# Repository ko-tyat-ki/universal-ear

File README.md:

# Nowhere Ear

```
Isn't he a bit like you and me?
Nowhere man, The world is at your command
```
## Introduction

You all know that we, the Ko-Tyat-Ki Kollektive, are working on this crazy
installation **EAR OF THE UNIVERSE** that will be (wooop wooop)
premiered at Nowhere 2019.

How do you create visuals for an installation you can't practically build at home?
That is correct, as a Full Stack dev, you create a web-simulation of the
real installation you can practice your code on 😆.

And then you ask all your friends to contribute!

## About the installation

The principle is:
a lot of ropes, when people touch them or pull them, the LEDs and
sound-scape changes.

How the light changes can be decided by you!

In this simulation, you can simulate pulling the ropes by
pressing keys on the keyboard, and see the results on the web page.

## Your contribution!

We worked very hard to make a potential contribution as easy as possible.
All the visualisation, simulation is there, but we need your ideas on how
to transform sensor data into lit LEDs.

This is basically to create a bit of a transformation code in between.

We did come up with several examples that represent what potantially can be done.
We hope they will be helpful, but please feel free to go wild.

When we recieve all the beautiful ideas, we will select the best, and figure out the
way to present them (e.g. one stick per idea? or one hour gig for each idea?)

And your idea and your name will be on Playa making all of nobodies super happy.

_(more details and explanations on where and how exactly to fill your idea in below)_

## Pre-requirements

Very basic knowledge of any coding and github should be enough.

Technical prerequisites: [github account](https://help.github.com/en/articles/connecting-to-github-with-ssh), computer with installed and [set up git](https://git-scm.com/book/en/v2/Getting-Started-First-Time-Git-Setup), [node and npm](https://www.npmjs.com/get-npm) (we use node 10).

## As a start
```
git clone git@github.com:ko-tyat-ki/nowhere-ear.git
cd nowhere-ear
npm install
npm start
```

This will start node server that will restart when you change the code.
Code can be written using es2015 syntax on server and on client.

When starting the server you might notice some warnings in the console, e.g.
```
Warning: the port /dev/tty/.usbmodem14201 failed to open, did you connect the device? If not - no worries, client side can work without it
```
Do not worry, this is for us to monitor the real devices we sometimes connect. The simulation can work without them.

#### To see the results
Navigate to http://localhost:3000 in your browser and enjoy the visualisation:

You can see three *structure types*: "Duet", "Circle" and "Realistic".
"Realistic" is the main one that is very similar to our latest plans for the real thing. Scaffolding position are close to what we are planning in reality. LEDs position are indicative, and might change - so this is mainly for you to have an idea / rough understanding how it is going to look. It will look much cooler with sensors highlighting fluorescent ropes and stuff (hopefully).

To "trigger" the sensor you can use keys "a" and "s" for "Duet", and
"1","2","3","4","5","6","7","8","9","0" for "Circle" and "Realistic".

We did simulate two types of interaction - very fast one, similar to abruptly pulling
the rope (keep the key on for a short period of time), and smooth one (keep key for a bit longer).

You can already choose several visual *modes* - functions that transform sensor data into lit leds. These are very basic examples of what potentially can be done (more about this below).

## How to contribute

### How can you add a new visualisation
1. Create a new branch with a name for example `[your-name]-[mode-name]` e.g. `katya-supermegacoolmode`

```
git checkout -b [your-name]-[mode-name]
```

2. Go to the folder `./web/lib/modes/`. This is where all visual modes live. Create a js file where your code will live (the easiest might be by copying one of the existing ones?).

3. Import it into `./web/lib/visualisations.js` by adding

```js
import [yourMode] from './modes/[yourMode]'
```

and the name of it to export.

4. Add a new mode under the same name `./static/index.html` under `<h5>mode:</h5>`

```html
<option value="yourMode">How you want to show your mode</option>
```

5. When you are happy with what you've done, create a Pull Request, and tag some of us.

### A bit more about modes

Modes function accepts `(sticks, sensors)`.

From sticks you can use properties that are set on config, such as
- `name`
- `numberOfLEDs`
- inital coordinates (y is vertical)
```js
init : {
    x: ...,
    y: ...,
    z: ...
}
```
Senors have
 - `tension` - the tension that depends on key press. There are two distinct tension modes,
 -- if the user releases the key after less than 0.5s pressing, the sensor gets quickly to the highest value and back
 -- if the user continues pressing the key after 0.5s, the sensor value slowly increases, and slowly decreases after the button is released
 - `oldTension` - an array of tension history (four values slowly following the current tension value: [0] the furthest away from tension value, [3] the closest value)
 - `stick` - which column (stick) it is attached to
 - `position` - where on the stick it is attached to; as a number of the LED

The function should return array of arrays, where every entry has
- `key` - name of the stick you want to light up
- array of `leds`.

Every led has its `number` (integer, from `0` to `numberOfLEDs-1`) and color
```js
color : {
    r: ...,
    g: ...,
    b: ...
}
```

Everything else is up to your imagination.

## A bit more about existing examples

### Basic

Simply reacts to sensor tension proportionate to tension. Very basic.

### Fast reaction

Reacts only to fast pull and does not to slow one.

### Flicker

Flickers the stick when you activate the sensor attahced to it.

### Random echo

The active stick is the brightest, all the rest are less bright proportinate to the distance.

### Tension with echo

When tension reached the end of the stick, its echo goes to all other sticks.

## Support and questions

Any questions, suggestions, love notes - write them either to Katya or Ivan immediately via
any known source of commmunication, or submit a github issue.

## API

### Switch mode

Path: `/mode`
Method: `POST`
Headers: `Content-Type: application/json`
Body Example:
```
{
  "method": "flicker"
}
```

Available modes:
```
basic
basic_with_rainbow
changing_colors
fastReaction
flicker
rain
rainEffect
random_flashes
randomEcho
tensionWithEcho
workshop
```

## Helpful commands
To list connected USB devices
```
ls /dev/tty*
```
To get the sound working run in the parallel terminal
```
python3 ./sound/run_sound.py
```
Make sure you have `pygame` installed. If you see an error message
`ImportError: No module named pygame` 
```
python -m ensurepip --user
/Library/Developer/CommandLineTools/usr/bin/python3 -m pip install --upgrade pip
python -m pip install pygame
```
Connect to PI SD card from comp:
```
sudo kextunload -b io.macfuse.filesystems.macfuse
sudo fuse-ext2 /dev/disk4s2 /Volumes/raspberry -o rw+
```
## How to change wifi data
```
cd /Volumes/raspberry/home/pi/nowhere-ear/deploy/pi-settings
vim wpa_supplicant.conf
```
Then
```
cd /
sudo umount /Volumes/raspberry
```
Sometimes you have to relogin to pi, passowrd is `raspberry`

sudo amixer cset numid=1 90%

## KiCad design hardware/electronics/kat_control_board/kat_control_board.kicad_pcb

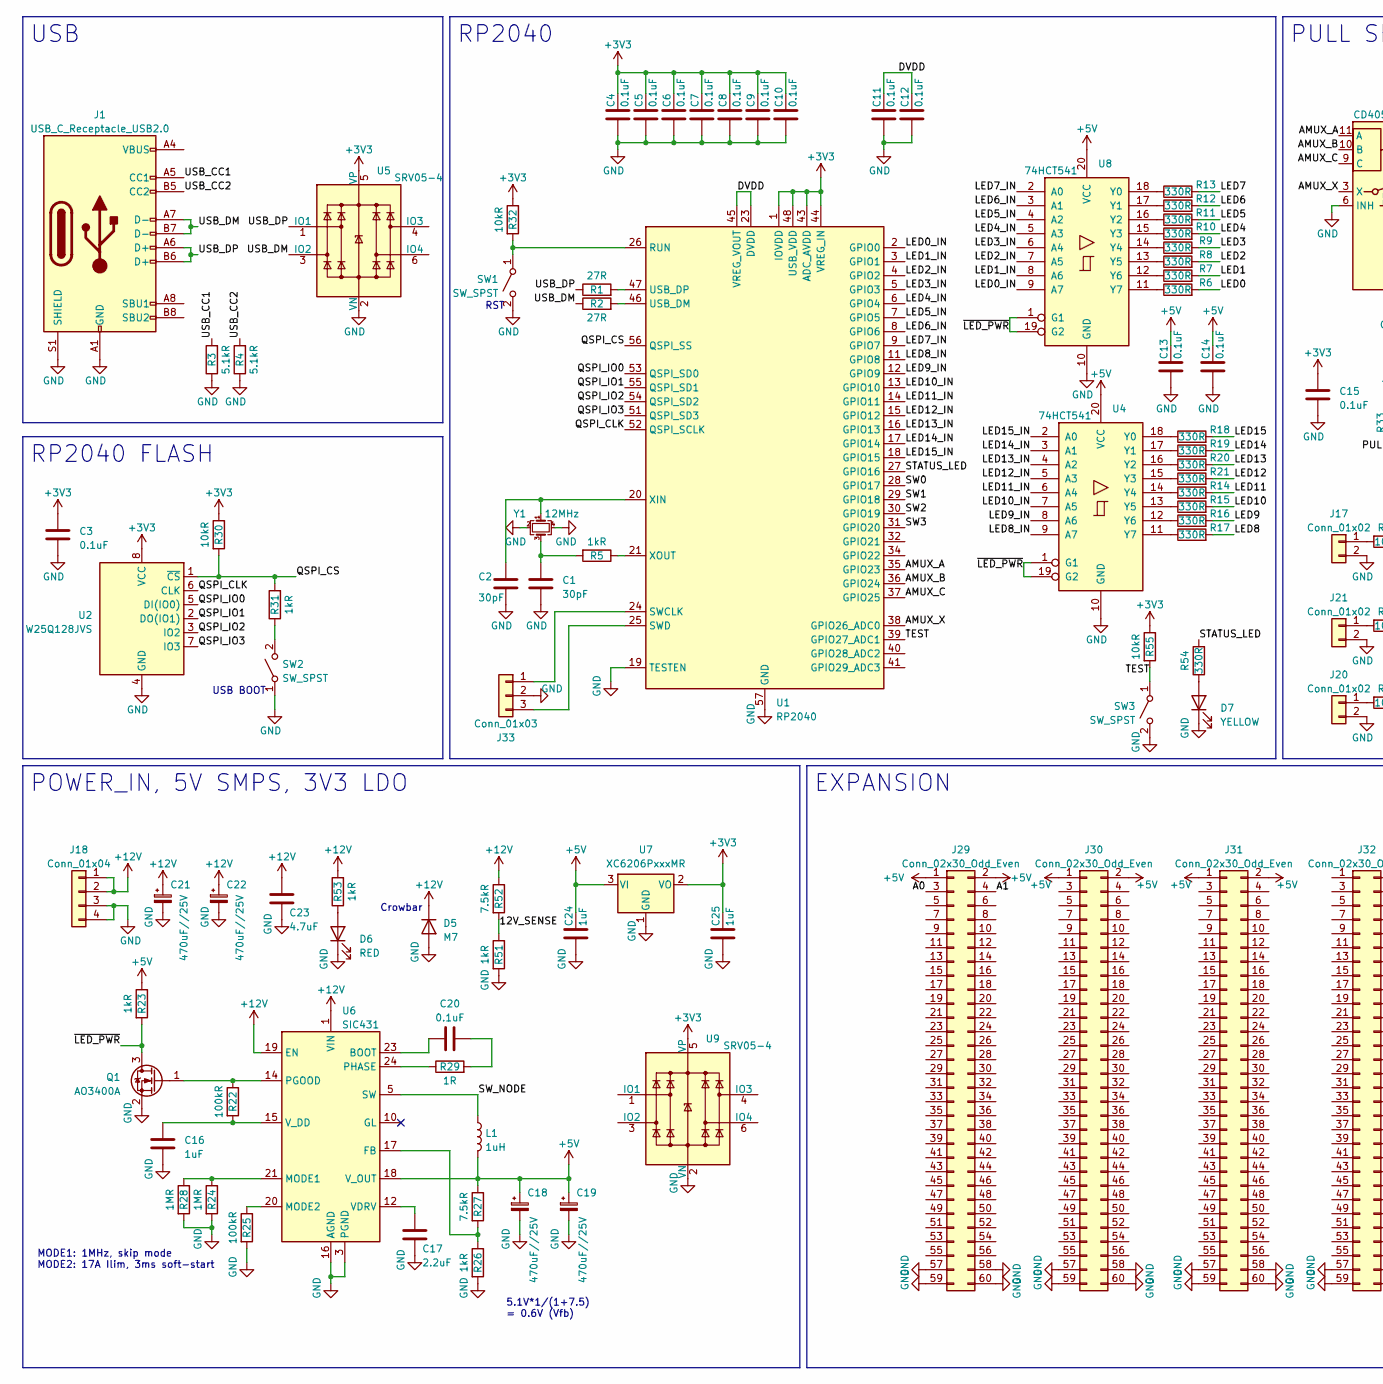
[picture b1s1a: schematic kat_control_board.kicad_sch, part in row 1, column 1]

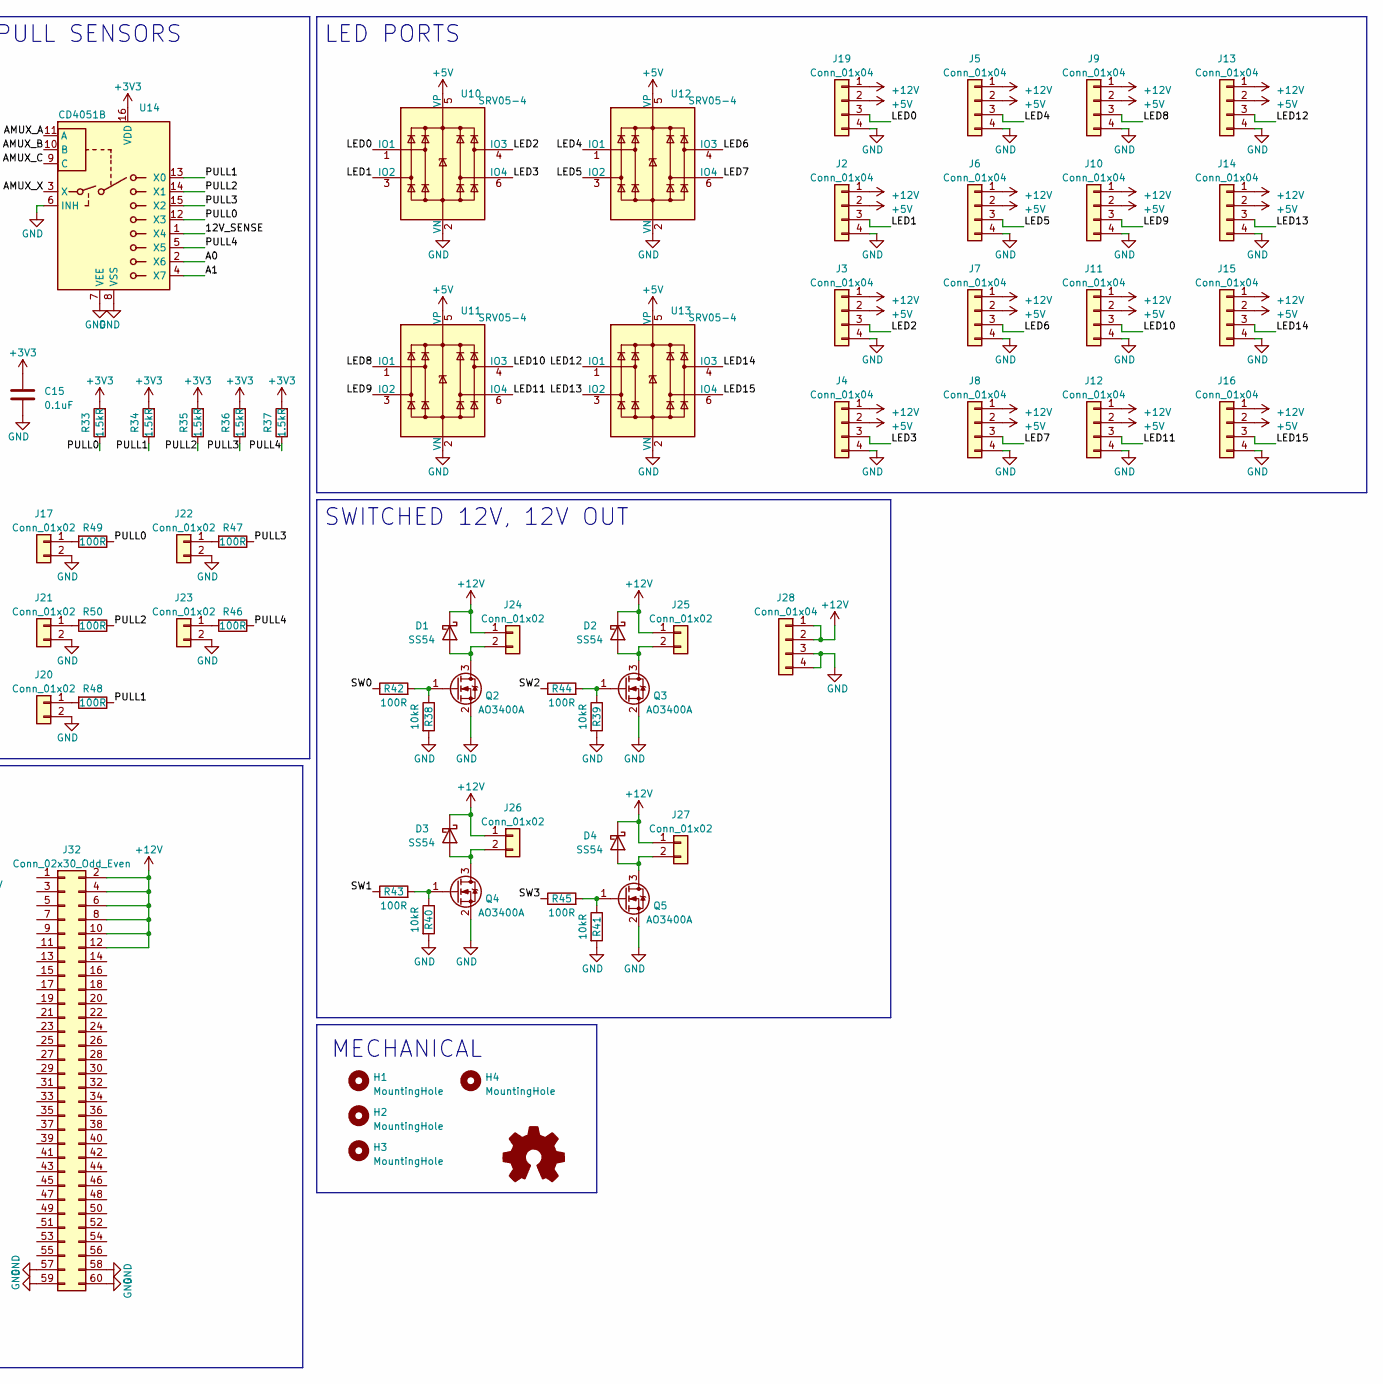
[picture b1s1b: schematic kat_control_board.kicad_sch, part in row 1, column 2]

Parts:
C1, C2: 30pF; C_0402_1005Metric; JLC C1570
C3, C4, C5, C6, C7, C8, C9, C10, C11, C12, C13, C14, C15: 0.1uF; C_0402_1005Metric; JLC C1525
C16, C24, C25: 1uF; C_0402_1005Metric; JLC C52923
C17: 2.2uF; C_0603_1608Metric; JLC C23630
C18, C19, C21, C22: 470uF//25V; CP_Radial_D6.3mm_P2.50mm; JLC C2938714
C20: 0.1uF; C_0402_1005Metric; JLC C307331
C23: 4.7uF; C_0603_1608Metric; JLC C19666
D1, D2, D3, D4: SS54; D_SMA; LCSC C22452
D5: M7; D_SMA; LCSC C95872
D6: RED; LED_0603_1608Metric; LCSC C2286
D7: YELLOW; LED_0603_1608Metric; LCSC C72038
H1, H2, H3, H4: MountingHole; MountingHole_3.5mm_Pad_Via
J1: USB_C_Receptacle_USB2.0; USB_C_Receptacle_HRO_TYPE-C-31-M-12; JLC C165948
J2, J3, J4, J5, J6, J7, J8, J9, J10, J11, J12, J13, J14, J15, J16, J18, J19, J28: Conn_01x04; DB2ERC-3.5-4P; JLC C395831
J17, J20, J21, J22, J23, J24, J25, J26, J27: Conn_01x02; DB2ERC-3.5-2P; LCSC C395830
J29, J30, J31, J32: Conn_02x30_Odd_Even; PinHeader_2x30_P2.54mm_Vertical
J33: Conn_01x03; PinHeader_1x03_P2.54mm_Vertical
L1: 1uH; CKST1004; JLC C3002679
LOGO1: Logo_Open_Hardware_Small; kinki_yokai_logo
Q1: AO3400A; SOT-23; JLC C20917
Q2, Q3, Q4, Q5: AO3400A; SOT-23; LCSC C20917
R1, R2: 27R; R_0603_1608Metric; JLC C25190
R3, R4: 5.1kR; R_0402_1005Metric; JLC C105872
R5, R23, R26, R31, R51, R53: 1kR; R_0402_1005Metric; JLC C11702
R6, R7, R8, R9, R10, R11, R12, R13, R14, R15, R16, R17, R18, R19, R20, R21, R54: 330R; R_0402_1005Metric; JLC C25104
R22: 100kR; R_0402_1005Metric; JLC C25086
R24, R28: 1MR; R_0402_1005Metric; JLC C26083
R25: 100kR; R_0402_1005Metric; JLC C25741
R27, R52: 7.5kR; R_0402_1005Metric; JLC C25918
R29: 1R; R_0402_1005Metric; JLC C25086
R30, R32, R38, R39, R40, R41, R55: 10kR; R_0402_1005Metric; JLC C25086
R33, R34, R35, R36, R37: 1.5kR; R_0402_1005Metric; JLC C25867
R42, R43, R44, R45, R46, R47, R48, R49, R50: 100R; R_0402_1005Metric; JLC C25076
SW1, SW2, SW3: SW_SPST; TS-1187A-B-A-B; JLC C318884
U1: RP2040; QFN-56-1EP_7x7mm_P0.4mm_EP3.2x3.2mm; JLC C2040
U2: W25Q128JVS; SOIC-8_5.23x5.23mm_P1.27mm; JLC C97521
U4, U8: 74HCT541; TSSOP-20_4.4x6.5mm_P0.65mm; LCSC C436096
U5, U9, U10, U11, U12, U13: SRV05-4; SOT-23-6; LCSC C85364
U6: SIC431; Vishay_PowerPAK_MLP44-24L_ThermalVias; LCSC C2071422
U7: XC6206PxxxMR; SOT-23-3; LCSC C5446
U14: CD4051B; SOIC-16_3.9x9.9mm_P1.27mm; LCSC C21379
Y1: 12MHz; Crystal_SMD_3225-4Pin_3.2x2.5mm; JLC C9002

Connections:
+3V3: C3.1, C4.1, C5.1, C6.1, C7.1, C8.1, C9.1, C10.1, C15.1, C25.1, R30.1, R32.1, R33.2, R34.2, R35.2, R36.2, R37.2, R55.1, U1.1 (IOVDD), U1.10 (IOVDD), U1.22 (IOVDD), U1.33 (IOVDD), U1.42 (IOVDD), U1.43 (ADC_AVDD), U1.44 (VREG_IN), U1.48 (USB_VDD), U1.49 (IOVDD), U2.8 (VCC), U5.5 (VP), U7.2 (VO), U9.5 (VP), U14.16 (VDD)
+5V: C13.1, C14.1, C18.1, C19.1, C24.1, J2.2, J3.2, J4.2, J5.2, J6.2, J7.2, J8.2, J9.2, J10.2, J11.2, J12.2, J13.2, J14.2, J15.2, J16.2, J19.2, J29.1, J29.2, J30.1, J30.2, J31.1, J31.2, L1.2, R23.1, R27.1, U4.20 (VCC), U6.18 (V_OUT), U7.3 (VI), U8.20 (VCC), U10.5 (VP), U11.5 (VP), U12.5 (VP), U13.5 (VP)
+12V: C21.1, C22.1, C23.1, D1.1 (K), D2.1 (K), D3.1 (K), D4.1 (K), D5.1 (K), J2.1, J3.1, J4.1, J5.1, J6.1, J7.1, J8.1, J9.1, J10.1, J11.1, J12.1, J13.1, J14.1, J15.1, J16.1, J18.1, J18.2, J19.1, J24.1, J25.1, J26.1, J27.1, J28.1, J28.2, J32.2, J32.4, J32.6, J32.8, J32.10, J32.12, R52.1, R53.2, U6.1 (VIN), U6.2 (VIN), U6.19 (EN), U6.22 (VIN), U6.26 (VIN)
/12V_SENSE: R51.1, R52.2, U14.1 (X4)
/A0: J29.3, U14.2 (X6)
/A1: J29.4, U14.4 (X7)
/AMUX_A: U1.35 (GPIO23), U14.11 (A)
/AMUX_B: U1.36 (GPIO24), U14.10 (B)
/AMUX_C: U1.37 (GPIO25), U14.9 (C)
/AMUX_X: U1.38 (GPIO26_ADC0), U14.3 (X)
/DVDD: C11.1, C12.1, U1.23 (DVDD), U1.45 (VREG_VOUT), U1.50 (DVDD)
/LED0: J19.3, R6.2, U10.1 (IO1)
/LED0_IN: U1.2 (GPIO0), U8.9 (A7)
/LED1: J2.3, R7.2, U10.3 (IO2)
/LED1_IN: U1.3 (GPIO1), U8.8 (A6)
/LED2: J3.3, R8.2, U10.4 (IO3)
/LED2_IN: U1.4 (GPIO2), U8.7 (A5)
/LED3: J4.3, R9.2, U10.6 (IO4)
/LED3_IN: U1.5 (GPIO3), U8.6 (A4)
/LED4: J5.3, R10.2, U12.1 (IO1)
/LED4_IN: U1.6 (GPIO4), U8.5 (A3)
/LED5: J6.3, R11.2, U12.3 (IO2)
/LED5_IN: U1.7 (GPIO5), U8.4 (A2)
/LED6: J7.3, R12.2, U12.4 (IO3)
/LED6_IN: U1.8 (GPIO6), U8.3 (A1)
/LED7: J8.3, R13.2, U12.6 (IO4)
/LED7_IN: U1.9 (GPIO7), U8.2 (A0)
/LED8: J9.3, R17.2, U11.1 (IO1)
/LED8_IN: U1.11 (GPIO8), U4.9 (A7)
/LED9: J10.3, R16.2, U11.3 (IO2)
/LED9_IN: U1.12 (GPIO9), U4.8 (A6)
/LED10: J11.3, R15.2, U11.4 (IO3)
/LED10_IN: U1.13 (GPIO10), U4.7 (A5)
/LED11: J12.3, R14.2, U11.6 (IO4)
/LED11_IN: U1.14 (GPIO11), U4.6 (A4)
/LED12: J13.3, R21.2, U13.1 (IO1)
/LED12_IN: U1.15 (GPIO12), U4.5 (A3)
/LED13: J14.3, R20.2, U13.3 (IO2)
/LED13_IN: U1.16 (GPIO13), U4.4 (A2)
/LED14: J15.3, R19.2, U13.4 (IO3)
/LED14_IN: U1.17 (GPIO14), U4.3 (A1)
/LED15: J16.3, R18.2, U13.6 (IO4)
/LED15_IN: U1.18 (GPIO15), U4.2 (A0)
/PULL0: R33.1, R49.1, U14.12 (X3)
/PULL1: R34.1, R48.1, U14.13 (X0)
/PULL2: R35.1, R50.1, U14.14 (X1)
/PULL3: R36.1, R47.1, U14.15 (X2)
/PULL4: R37.1, R46.1, U14.5 (X5)
/QSPI_CLK: U1.52 (QSPI_SCLK), U2.6 (CLK)
/QSPI_CS: R30.2, R31.2, U1.56 (QSPI_SS), U2.1 (~CS)
/QSPI_IO0: U1.53 (QSPI_SD0), U2.5 (DI(IO0))
/QSPI_IO1: U1.55 (QSPI_SD1), U2.2 (DO(IO1))
/QSPI_IO2: U1.54 (QSPI_SD2), U2.3 (IO2)
/QSPI_IO3: U1.51 (QSPI_SD3), U2.7 (IO3)
/STATUS_LED: R54.2, U1.27 (GPIO16)
/SW0: R42.1, U1.28 (GPIO17)
/SW1: R43.1, U1.29 (GPIO18)
/SW2: R44.1, U1.30 (GPIO19)
/SW3: R45.1, U1.31 (GPIO20)
/SW_NODE: L1.1, U6.5 (SW), U6.6 (SW), U6.7 (SW), U6.8 (SW), U6.9 (SW)
/TEST: R55.2, SW3.1 (A), U1.39 (GPIO27_ADC1)
/USB_CC1: J1.A5 (CC1), R3.2
/USB_CC2: J1.B5 (CC2), R4.2
/USB_DM: J1.A7 (D-), J1.B7 (D-), R2.1, U5.3 (IO2)
/USB_DP: J1.A6 (D+), J1.B6 (D+), R1.1, U5.1 (IO1)
/~LED_PWR: Q1.3 (D), R23.2, U4.1 (G1), U4.19 (G2), U8.1 (G1), U8.19 (G2)
GND: C1.2, C2.2, C3.2, C4.2, C5.2, C6.2, C7.2, C8.2, C9.2, C10.2, C11.2, C12.2, C13.2, C14.2, C15.2, C16.2, C17.2, C18.2, C19.2, C21.2, C22.2, C23.2, C24.2, C25.2, D5.2 (A), D6.1 (K), D7.1 (K), J1.A1 (GND), J1.A12 (GND), J1.B1 (GND), J1.B12 (GND), J1.S1 (SHIELD), J2.4, J3.4, J4.4, J5.4, J6.4, J7.4, J8.4, J9.4, J10.4, J11.4, J12.4, J13.4, J14.4, J15.4, J16.4, J17.2, J18.3, J18.4, J19.4, J20.2, J21.2, J22.2, J23.2, J28.3, J28.4, J29.57, J29.58, J29.59, J29.60, J30.57, J30.58, J30.59, J30.60, J31.57, J31.58, J31.59, J31.60, J32.57, J32.58, J32.59, J32.60, J33.2, Q1.2 (S), Q2.2 (S), Q3.2 (S), Q4.2 (S), Q5.2 (S), R3.1, R4.1, R24.2, R25.2, R26.2, R28.2, R38.2, R39.2, R40.2, R41.2, R51.2, SW1.2 (B), SW2.1 (A), SW3.2 (B), U1.19 (TESTEN), U1.57 (GND), U2.4 (GND), U4.10 (GND), U5.2 (VN), U6.3 (PGND), U6.4 (PGND), U6.13 (PGND), U6.16 (AGND), U6.25 (AGND), U6.27 (PGND), U7.1 (GND), U8.10 (GND), U9.2 (VN), U10.2 (VN), U11.2 (VN), U12.2 (VN), U13.2 (VN), U14.6 (INH), U14.7 (VEE), U14.8 (VSS), Y1.2, Y1.4
unnamed: C1.1, R5.2, Y1.3
unnamed: C20.2, R29.2
unnamed: D1.2 (A), J24.2, Q2.3 (D)
unnamed: D2.2 (A), J25.2, Q3.3 (D)
unnamed: D3.2 (A), J26.2, Q4.3 (D)
unnamed: D4.2 (A), J27.2, Q5.3 (D)
unnamed: D6.2 (A), R53.1
unnamed: D7.2 (A), R54.1
unnamed: J1.A4 (VBUS), J1.A9 (VBUS), J1.B4 (VBUS), J1.B9 (VBUS)
unnamed: J17.1, R49.2
unnamed: J20.1, R48.2
unnamed: J21.1, R50.2
unnamed: J22.1, R47.2
unnamed: J23.1, R46.2
unnamed: J33.1, U1.24 (SWCLK)
unnamed: J33.3, U1.25 (SWD)
unnamed: Q1.1 (G), R22.1, U6.14 (PGOOD)
unnamed: Q2.1 (G), R38.1, R42.2
unnamed: Q3.1 (G), R39.1, R44.2
unnamed: Q4.1 (G), R40.1, R43.2
unnamed: Q5.1 (G), R41.1, R45.2
unnamed: R32.2, SW1.1 (A), U1.26 (RUN)
unnamed: R31.1, SW2.2 (B)
unnamed: R2.2, U1.46 (USB_DM)
unnamed: R1.2, U1.47 (USB_DP)
unnamed: C2.1, U1.20 (XIN), Y1.1
unnamed: R5.1, U1.21 (XOUT)
unnamed: R18.1, U4.18 (Y0)
unnamed: R19.1, U4.17 (Y1)
unnamed: R20.1, U4.16 (Y2)
unnamed: R21.1, U4.15 (Y3)
unnamed: R14.1, U4.14 (Y4)
unnamed: R15.1, U4.13 (Y5)
unnamed: R16.1, U4.12 (Y6)
unnamed: R17.1, U4.11 (Y7)
unnamed: C20.1, U6.23 (BOOT)
unnamed: R26.1, R27.2, U6.17 (FB)
unnamed: R24.1, R28.1, U6.21 (MODE1)
unnamed: R25.1, U6.20 (MODE2)
unnamed: R29.1, U6.24 (PHASE)
unnamed: C17.1, U6.12 (VDRV)
unnamed: C16.1, R22.2, U6.15 (V_DD)
unnamed: R13.1, U8.18 (Y0)
unnamed: R12.1, U8.17 (Y1)
unnamed: R11.1, U8.16 (Y2)
unnamed: R10.1, U8.15 (Y3)
unnamed: R9.1, U8.14 (Y4)
unnamed: R8.1, U8.13 (Y5)
unnamed: R7.1, U8.12 (Y6)
unnamed: R6.1, U8.11 (Y7)

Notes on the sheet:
SWITCHED 12V, 12V OUT
LED PORTS
RP2040 FLASH
Crowbar
MODE1: 1MHz, skip mode MODE2: 17A Ilim, 3ms soft-start
EXPANSION
5.1V*1/(1+7.5) = 0.6V (Vfb)
USB BOOT
USB
PULL SENSORS
MECHANICAL
RST
POWER_IN, 5V SMPS, 3V3 LDO
RP2040

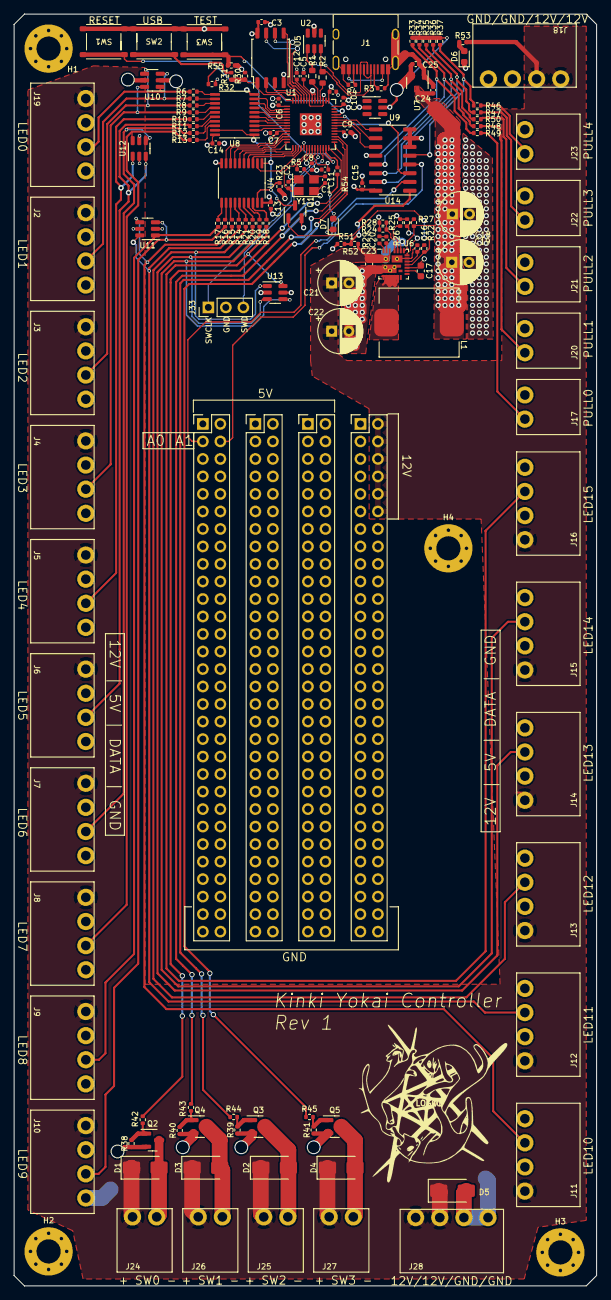
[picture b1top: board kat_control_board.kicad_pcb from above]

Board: 4 copper layers, 84.5 x 184.5 mm, 148 parts (0 on the bottom side), 117 nets.

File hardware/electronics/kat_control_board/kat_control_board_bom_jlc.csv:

"Comment","Designator","Footprint","LCSC Part #"
"30pF","C1,C2","C_0402_1005Metric","C1570"
"0.1uF","C3,C4,C5,C6,C7,C8,C9,C10,C11,C12,C13,C14,C15","C_0402_1005Metric","C1525"
"1uF","C16,C24,C25","C_0402_1005Metric","C52923"
"2.2uF","C17","C_0603_1608Metric","C23630"
"470uF//25V","C18,C19,C21,C22","CP_Radial_D6.3mm_P2.50mm","C2938714"
"0.1uF","C20","C_0402_1005Metric","C307331"
"4.7uF","C23","C_0603_1608Metric","C19666"
"SS54","D1,D2,D3,D4","D_SMA","C22452"
"USB_C_Receptacle_USB2.0","J1","USB_C_Receptacle_HRO_TYPE-C-31-M-12","C165948"
"Conn_01x04","J2,J3,J4,J5,J6,J7,J8,J9,J10,J11,J12,J13,J14,J15,J16,J18,J19,J28","DB2ERC-3.5-4P","C395831"
"Conn_01x02","J17,J20,J21,J22,J23,J24,J25,J26,J27","DB2ERC-3.5-2P","C395830"
"1uH","L1","CKST1004","C3002679"
"AO3400A","Q1,Q2,Q3,Q4,Q5","SOT-23","C20917"
"27R","R1,R2","R_0603_1608Metric","C25190"
"5.1kR","R3,R4","R_0402_1005Metric","C105872"
"1kR","R5,R23,R26,R31","R_0402_1005Metric","C11702"
"330R","R6,R7,R8,R9,R10,R11,R12,R13,R14,R15,R16,R17,R18,R19,R20,R21","R_0402_1005Metric","C25104"
"100kR","R22","R_0402_1005Metric","C25086"
"1MR","R24,R28","R_0402_1005Metric","C26083"
"100kR","R25","R_0402_1005Metric","C25741"
"7.5kR","R27","R_0402_1005Metric","C25918"
"1R","R29","R_0402_1005Metric","C25086"
"10kR","R30,R32,R38,R39,R40,R41","R_0402_1005Metric","C25086"
"1.5kR","R33,R34,R35,R36,R37","R_0402_1005Metric","C25867"
"SW_SPST","SW1,SW2","TS-1187A-B-A-B","C318884"
"RP2040","U1","QFN-56-1EP_7x7mm_P0.4mm_EP3.2x3.2mm","C2040"
"W25Q128JVS","U2","SOIC-8_5.23x5.23mm_P1.27mm","C97521"
"SN74HC4851","U3","TSSOP-16_4.4x5mm_P0.65mm","C2673391"
"74HCT244","U4,U5","TSSOP-20_4.4x6.5mm_P0.65mm","C131088"
"SIC431","U6","Vishay_PowerPAK_MLP44-24L_ThermalVias","C2071422"
"XC6206PxxxMR","U7","SOT-23-3","C5446"
"12MHz","Y1","Crystal_SMD_3225-4Pin_3.2x2.5mm","C9002"

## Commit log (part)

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2019-06-09 Move constant to a separate config (#34)
    * Move constant to a separate config
    * Remove old comments
2019-06-09 Previous tension (#35)
    * Add old tension
    * Smoothen previous tensions with rain
2019-06-09 First try to integrate real sensor class
    Needed to be thoroughly tested with the live devices
2019-06-09 Previous tension (#36)
    * Add old tension
    * Smoothen previous tensions with rain
    * arduino update
2019-06-09 Basic does work
2019-06-09 Flicker works as well
2019-06-09 Real sensor class (#37)
    * First draft of the realSensor class
    * First try to integrate real sensor class
    Needed to be thoroughly tested with the live devices
    * Fix the merge conflicts
    * Basic does work
    * Flicker works as well
2019-06-09 sensor old data updated
2019-06-09 clean arduino sensors
    Combination wouldn't work until we decouple the sensor power and leds power
2019-06-10 Remove sensitive data
2019-06-10 Working commit
2019-06-11 Best commit message ever - :new_moon_with_face: :cow:
2019-06-13 Realise yanns idea with sinus
    To check there is no limitations for its realisation
2019-06-14 Working version for mac!
2019-06-14 Tiny refactor
2019-06-15 remove non-used function
2019-06-15 Communicate with python
    Uses 'net' from node side and 'socket' in Python using port 8124.
    Writes a string with required data. Python reads string (this
    can be changes to buffer or Unit8Array if necessary.
    Code live is a separate helper file
2019-06-16 Spacing, sorry
2019-06-16 Make work without client (#44)
    * Spacing, sorry
    * Make it work without trigger from the client
    Previously it couldn't start writing becase ledsConfig were undefined
    Right now we assign an initial config value of []
2019-06-17 Rain updated
2019-06-17 And .... it does work!!!
2019-06-18 Make path to client io relative
2019-06-18 JS IS COMPLICATED
2019-06-18 Updated Rain and Flicker
2019-06-19 Smooth between 5-led-unit
2019-06-19 adding the rainbowColors function to the basic example: it loops colors with the rainbow logic and is sensor independent. The idea is it can be compatible with any other mode and add colors into the 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
2019-06-19 Add initial position to real sticks
2019-06-19 Realise yanns idea with sinus (#42)
    To check there is no limitations for its realisation
2019-06-19 some small fixes
2019-06-20 Added start up script that uses nvm because turned out that npm contains reference to system node and that nonsense ruins
2019-06-21 fail
2019-06-21 Add rainbow to yann
2019-06-21 random flashes adjustment
2019-06-21 stolbi
2019-06-23 Changes from my laptop that were during party
2019-06-23 Workaround for undefined stick in visualization Latest arduinosConfig:w
2019-06-23 Changes during party (#51)
    * Workaround for undefined stick in visualization
    Latest arduinosConfig:w
    * Delete non-used functions
    These function will be added as part of a separate PR
2019-06-23 realSticks
2019-06-23 no set timeout
2019-06-25 Added handler to configure modes on server Documented it
2019-06-25 Arduino changes
    Updated slow and fast sensor data;
    Three sensors file created
    Old arduino files deleted
2019-06-25 Three sensor Arduino. Refactoring
2019-06-25 Linting
2019-06-26 Fix fast and slow
2019-06-27 Automatic mode switching Added api for turning on automatic mode switching and configure switch timeout
2019-06-27 - reqs.txt - Python part harness
2019-06-27 Python code for mode processing
2019-06-28 Remove old comment
2019-06-28 Fix bug with yanns mode (auto switch)
2019-06-28 Fix couple of weird bugs in python
2019-06-28 Send info to python every 100ms
2019-06-28 Fix undefined for fast of the real sensor
2019-06-28 - flicker music
2019-06-28 change trigger value from test to realistic
2019-06-28 Fix resolution
2019-06-28 Send the real fake data to python
2019-06-28 replace all columns with sticks
2019-06-29 UV control; 3 sensors maximum output
2019-06-29 Ivan experiences / Arduinos (#53)
    * Improve regroupconfig
    * clean arduino sensors
    Combination wouldn't work until we decouple the sensor power and leds power
    * Working commit
    * Rain updated
    * Updated Rain and Flicker
2019-06-29 Add config for new sensors
2019-06-29 changed paths so that not dependent on relative paths
2019-06-29 Remove non-used import
2019-06-29 updating to the latest master
2019-06-29 Save if stick is not found
2019-06-29 Some changes to randomFlashes
2019-06-30 New visuals (#57)
    * Tiny refactoring
    * Add final structure
    * Add config for new sensors
    * Add jasmine
    * Remove non-used import
    * Add y to getDistance
2019-06-30 Add color function to stairs
    TBD: check how it looks on real arduinos
2019-06-30 Add tesnsion algorythm for 2 sticks
2019-06-30 Make it work in prod
2019-06-30 Some small tweaks
2019-06-30 [hotfix] no prints in python
2019-06-30 Fix bagchok
2019-06-30 Rename mode?mode to mode?name
2019-06-30 Add arduinosStatusHandler
2019-06-30 Wording
2019-06-30 visualizations from Oleg
2019-06-30 Add onChange WIP
2019-07-01 Reflect the latest agreements about structure
2019-07-01 Reflect the latest agreements about structure (#59)
2019-07-01 After merge fix
2019-07-01 Config fastReaction
2019-07-01 Remove basic from view
2019-07-01 Remove other not-used modes
2019-07-01 Config jasmine
2019-07-01 Fix naming conflict
2019-07-01 Config polzunki
2019-07-01 Config random flashes 2
2019-07-01 Config stairs
2019-07-01 Separate modes config into the json file (#61)
    * Config fastReaction
    * Config basicWithRainbows
    * Remove basic from view
    * Config changingColors
    * Remove other not-used modes
    * Slightly change flicker
2019-07-01 Automatic mode switching (#54)
    * Automatic mode switching
    Added api for turning on automatic mode switching and configure switch timeout
    * Fix bagchok
    * Change changeMode from get to post
    * Rename mode?mode to mode?name
    * Add arduinosStatusHandler
2019-07-01 Add onChange to config
2019-07-01 easter egg mode added previous mode tracking couple of crotches in automatic mode switching
2019-07-02 Ooooops
2019-07-02 Fix for the server
    for the case when ledsConfig is empty at the beginning
2019-07-02 Add package-lock.json to .gitignore
2019-07-02 Revert change
2019-07-03 Change slow to fast
2019-07-03 - lite music, mp3
2019-07-04 - jasmine
2019-07-04 Clean modes we output to the client
2019-07-04 Tiny but of reshuffling
2019-07-04 Apply mode doesn't use any args
2019-07-04 Fix the way sleep works
2019-07-04 Remove comments and format
2019-07-04 Remove nont-used lines
2019-07-04 Remove sleep from visualisation
2019-07-04 Config real sticks
2019-07-04 Improve jasmine
2019-07-04 Fix easterEgg start
2019-07-04 Remove console.log
2019-07-04 Descrease autochenage time
2019-07-04 Move some of the setup to config
2019-07-04 Add factor to flicker
2019-07-04 My refactoring of modes (#66)
    * - lite music, mp3
    * Added sleep tracker module that contains logic for tracking sleeping and waking up conditions
    added sleep mode (paint all into black)
    setup server callbacks for sleep and wake up
    * - jasmine
    * Clean modes we output to the client
2019-07-04 EasterEgg requires 8 to burn
2019-07-04 Make checks rare (#67)
    * EasterEgg requires 8 to burn
    * Do mode cheks one in half a second
2019-07-04 Comment out modes
2019-07-04 Try to improve jasmine
2019-07-04 One more
2019-07-04 Switch the python back
2019-07-04 master update
2019-07-04 Change mode every 3 minutes
2019-07-04 Attemps to improve (#68)
    * Don't separate calcs in a sep func
    * Comment out modes
    * Try to comment out python
    * Try to improve jasmine
    * Another attemps
    * One more
2019-07-04 Olegs playground (#69)
    * Remove script that is not used
    * Rename functions into modes
    * Move configurations out of helpers
    * readme updated
    * readme updated + test mode
    * Add more about installation instructions
2019-07-04 Random echo optimisation Jasmine: a bit better condition for resetting randomness counter
2019-07-05 Tiny changingColor change
2019-07-05 ocean optimisation
2019-07-05 What if like this
2019-07-05 Awesome change
2019-07-05 Fix what goes to pi
2019-07-05 Fix easterEgg name
2019-07-05 - change folder name
2019-07-05 Test sleep
2019-07-05 control buttons on visualisation
2019-07-05 Add buttons style
2019-07-05 Add buttons
2019-07-05 Supa mobile (#72)
    * Add buttons
    * Fix the mode change
2019-07-05 Fix bug with the url mode switch
2019-07-05 Fix bugs (#74)
    * Fix bug with the url mode switch
    * Ooops
2019-07-05 Add a bit of logging
2019-07-05 Consistent naming
2019-07-05 And a fix (#75)
    * Pythons print mode
    * Consistent naming
    * Haha ooops
2019-07-05 Remove test logs
2019-07-05 - proper logging
2019-07-05 Sound lite (#76)
    * - lite music, mp3
    * - jasmine
    * - EasterEgg
    * - EasterEgg Camelcase
    * - Super-mega-easter-egg!
    * - change folder name
2019-07-05 Server is the only source of mode truth
    Mode is picked up randomly at the very beginning
2019-07-06 Handle non-existing names
2019-07-06 Remove non-used comments
2019-07-06 Fix modes (#77)
    * Remove comment in pi
    * Server is the only source of mode truth
    Mode is picked up randomly at the very beginning
    * Remove comment
    * Fix the sleepMode vs onChange
    * Handle non-existing names
2019-07-06 master merge
2019-07-06 - volume controls into config
2019-07-06 Remove unnecessary logs
2019-07-06 - polzynki
2019-07-06 - polzynki change level
2019-07-06 - polzynki change levels for some sounds, trigger at 0.5
2019-07-06 Make autoChange and sleep config realistic
2019-07-07 master
2019-07-07 Draft prod version of config
2019-07-07 Draft prod version of config (#81)
2019-07-07 - 2 new modes, all sounds finished, all code finished - config changed for 15 mins sleep and 10 mins change
2019-07-07 - 2 new modes, all sounds finished, all code finished (#82)
    - config changed for 15 mins sleep and 10 mins change
2019-11-08 Rename final structure into nowhere2019
2019-11-08 Clean structures choices on the client
    Keep only two realised ones, and two most basic ones for
    experementation.
    With the view to add more actual structures to the list
2019-11-08 Clean stairs mode
    Has special case for 2 sticks, and for other number of sticks work
    as if there are 12.
    Thus any structures < 12 will have this mode working
2019-11-08 Send number of channels to python
    This will allow to redistribute sound if number of columns is
    less than 12
2019-11-29 Keep nowhere as the primary structure
2022-08-29 Changed sound for 5 channels for MCF
2022-08-29 Changed some sounds
2022-08-31 latest changes
2022-09-01 change modes sensitivity
2022-10-05 tiny instructions change
2022-11-10 true letov
2023-05-26 Added rev1 PCB design
2023-05-26 Updated PCB routing
2023-05-29 Updated PCB design with more protections
2023-05-30 Added DRC exclusions
2023-06-11 Added fp-info-cache to gitignore
2023-06-13 Changed test firmware to use multi-transfer DMA
2023-07-14 Controller board WIP
2023-07-18 Fixed typo
2023-07-25 Improved flashing command and updated test_client to buffer messages
2023-07-28 Deleted pio bug repro firmware
2023-07-28 Implemented pull sensor IIR filtering and Fire2012
2023-07-28 Added fire support to protocol doc and test client
2023-07-28 Moved fire brightness multiplier to client side
2023-07-29 Added support for switched 12V outputs
2023-08-15 backwards compatibility fillers
2023-08-19 THINGS GO BLINK BLINK BLINK
2023-08-20 individually controlled strips, stips with no sensors, new modes, strip memory
2023-08-21 decay optimisation into null
2023-08-25 small additions
